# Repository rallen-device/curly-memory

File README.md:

# CURLY-MEMORY

Open source eurorack hardware using an ESP32.

ESP32 acts like anything you want, just reprogram with new firmware.

## Features

### INPUTS:
 - Analogue input x4
  - 1/8" jack x3 (IN0, IN1, IN2)
  - 2.54mm pin header x2 (IN2, IN3)

### OUTPUTS:
 - Analogue output x4
  - 1/8" jack x3 (OUT0, OUT1, OUT2)
  - 2.54mm pin header x3 (OUT2, OUT3)

### CONTROLS:
 - Potentiometer input x4
 - Tactile switch x2

### OTHER:
 - Feedback resistor (digital pot connecting OUT0 to IN0)
 - Digital pot output on 2.54mm pin header
 - Dry/wet mixer (IN0 + OUT0 - connecting to digital pot)
 - WS2812B LEDs x2

### POWER:
 - Eurorack standard 10 pin IDC connector
 - 12V input

### FIRMWARE:
 - ESP-IDF or Arduino

## Images

## References

- https://www.electrosmash.com/pt2399-analysis
- https://intellijel.com/support/eurorack-101/
- https://docs.espressif.com/projects/esp-idf/en/latest/esp32/api-reference/peripherals/spi_master.html

## Influences

- https://ornament-and-cri.me/

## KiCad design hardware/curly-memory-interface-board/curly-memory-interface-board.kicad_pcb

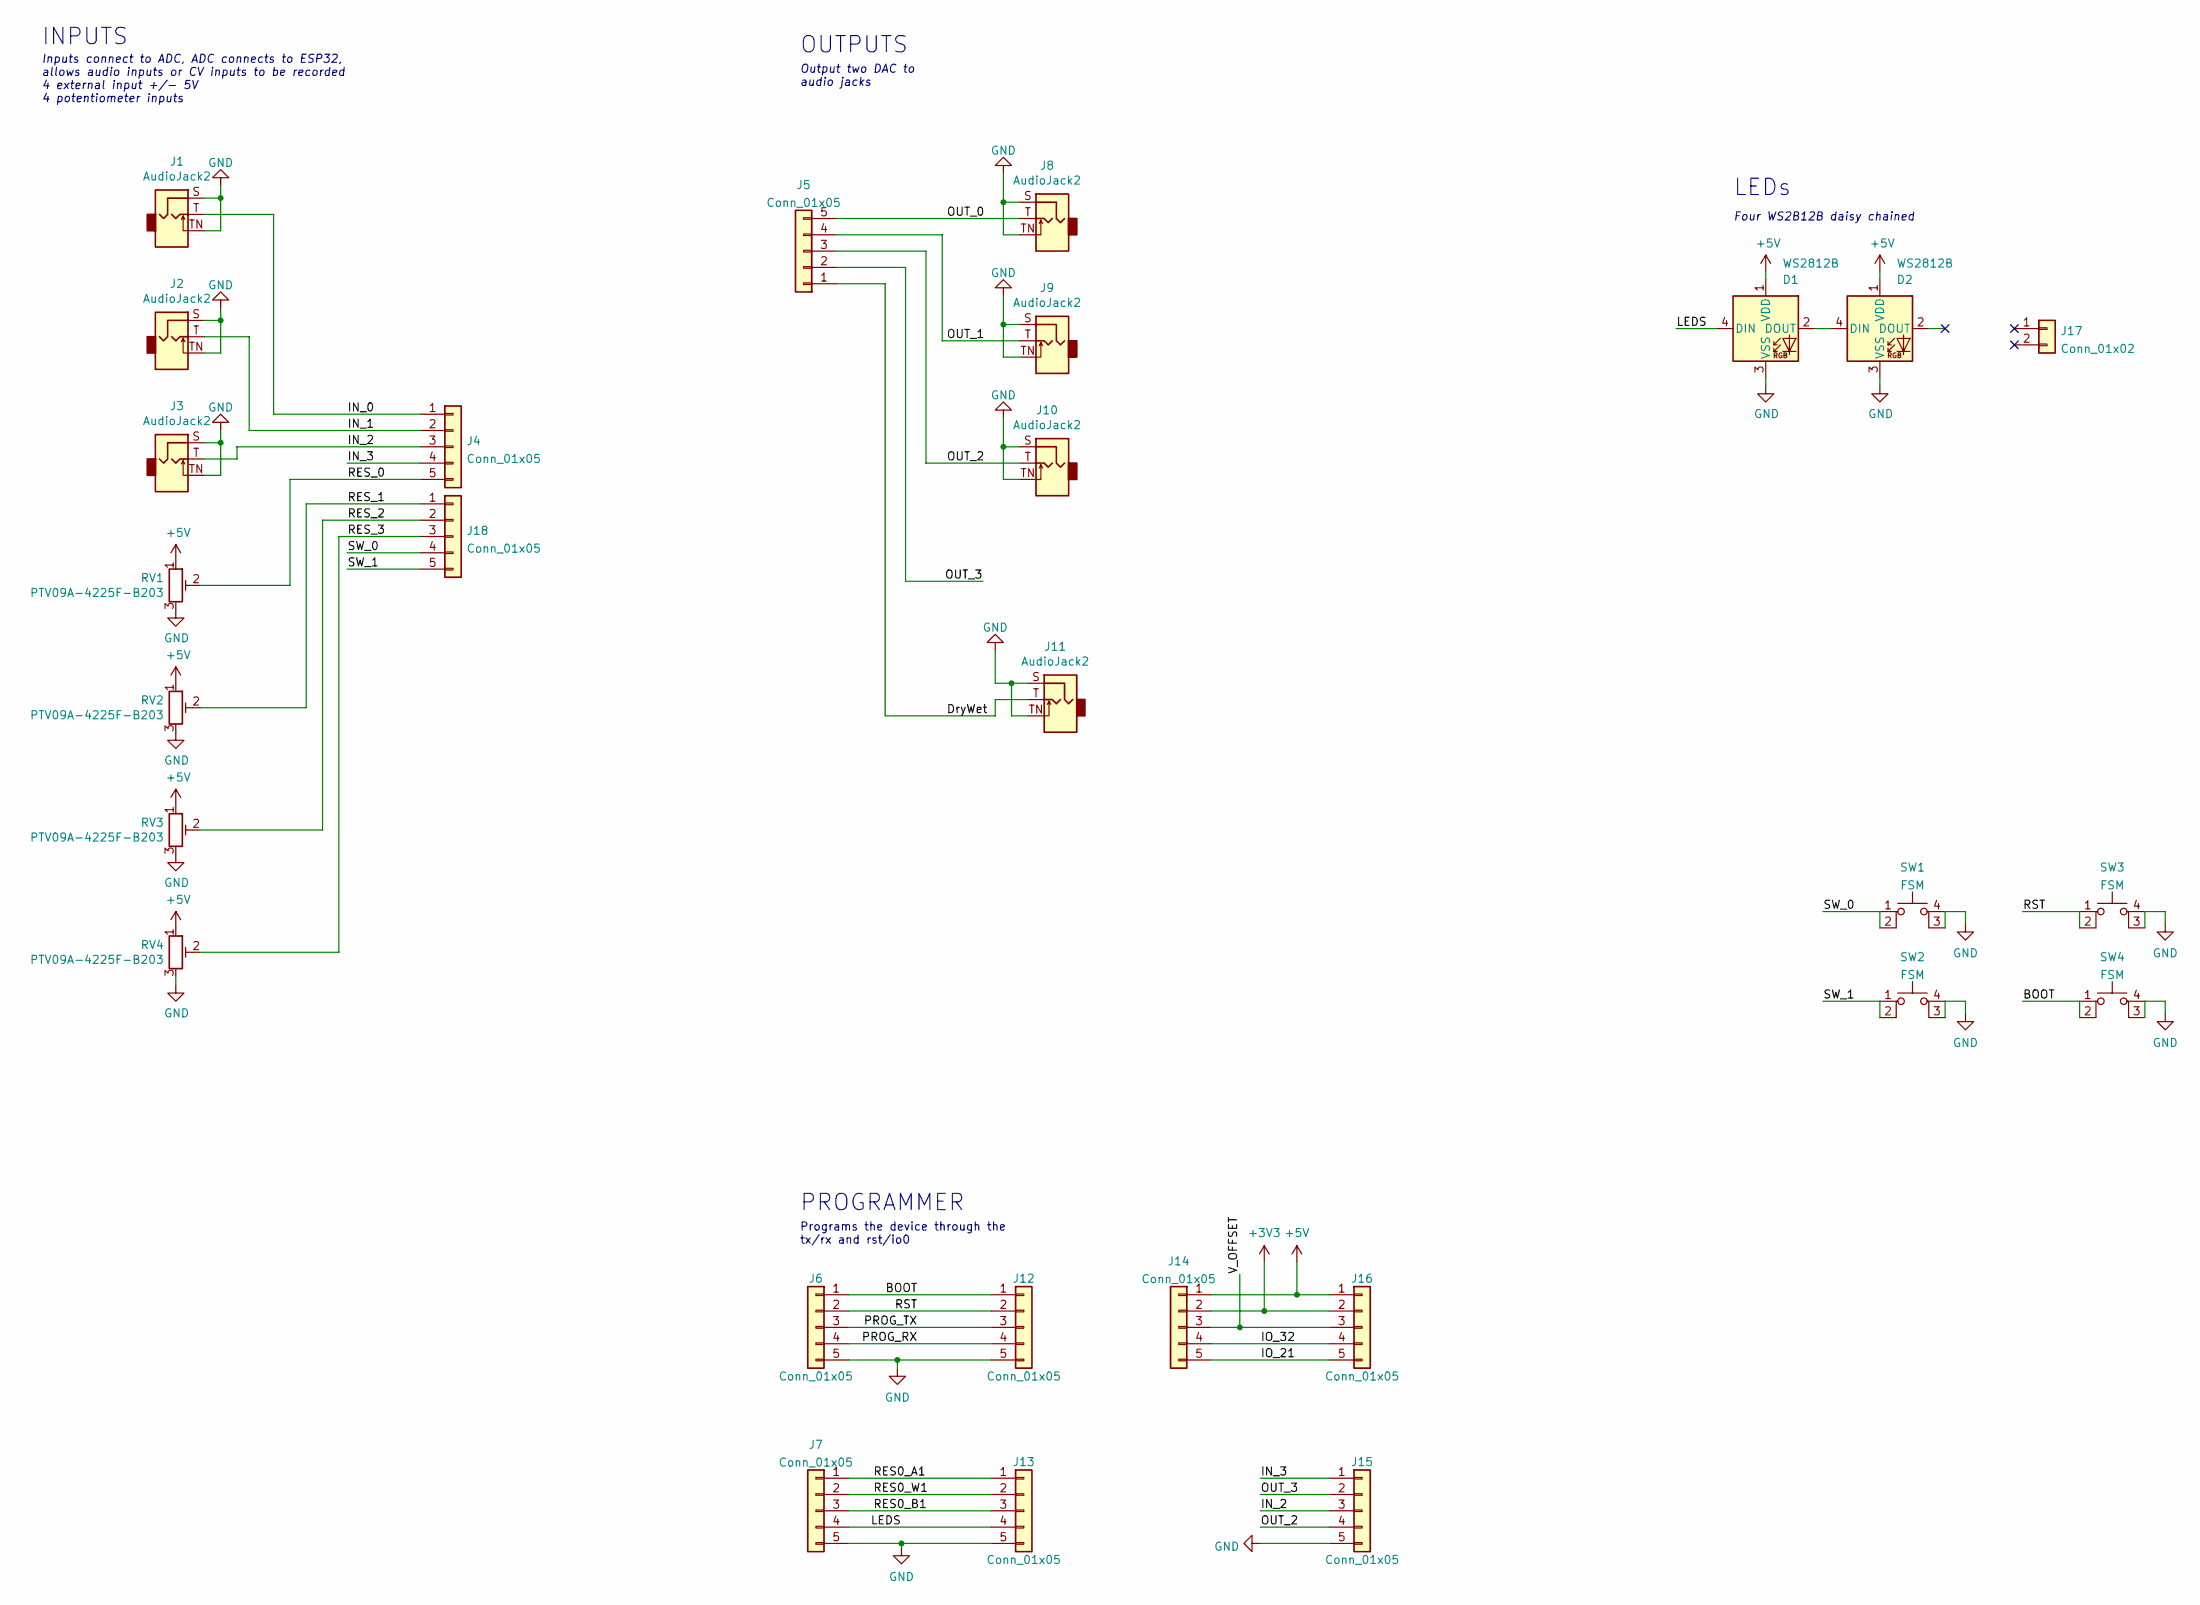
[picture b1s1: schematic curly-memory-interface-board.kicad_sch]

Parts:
D1, D2: WS2812B; LED_WS2812B_PLCC4_5.0x5.0mm_P3.2mm
J1, J2, J3, J8, J9, J10, J11: AudioJack2; Jack_3.5mm_QingPu_WQP-PJ398SM_Vertical
J4, J5, J6, J7, J14, J18: Conn_01x05; PinSocket_1x05_P2.54mm_Vertical
J12, J13, J15, J16: Conn_01x05; PinHeader_1x05_P2.54mm_Vertical
J17: Conn_01x02; PinSocket_1x02_P2.54mm_Vertical
RV1, RV2, RV3, RV4: PTV09A-4225F-B203; Potentiometer_Bourns_PTV09A-1_Single_Vertical
SW1, SW2, SW3, SW4: FSM; SW_Push_1P1T_NO_6x6mm_H9.5mm

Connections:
+3V3: J14.2, J16.2
+5V: D1.1 (VDD), D2.1 (VDD), J14.1, J16.1, RV1.1, RV2.1, RV3.1, RV4.1
/BOOT: J6.1, J12.1, SW4.1, SW4.2
/DryWet: J5.1, J11.T
/IN_0: J1.T, J4.1
/IN_1: J2.T, J4.2
/IN_2: J3.T, J4.3, J15.3
/IN_3: J4.4, J15.1
/IO_21: J14.5, J16.5
/IO_32: J14.4, J16.4
/LEDS: D1.4 (DIN), J7.4, J13.4
/OUT_0: J5.5, J8.T
/OUT_1: J5.4, J9.T
/OUT_2: J5.3, J10.T, J15.4
/OUT_3: J5.2, J15.2
/PROG_RX: J6.4, J12.4
/PROG_TX: J6.3, J12.3
/RES0_A1: J7.1, J13.1
/RES0_B1: J7.3, J13.3
/RES0_W1: J7.2, J13.2
/RES_0: J4.5, RV1.2
/RES_1: J18.1, RV2.2
/RES_2: J18.2, RV3.2
/RES_3: J18.3, RV4.2
/RST: J6.2, J12.2, SW3.1, SW3.2
/SW_0: J18.4, SW1.1, SW1.2
/SW_1: J18.5, SW2.1, SW2.2
/V_OFFSET: J14.3, J16.3
GND: D1.3 (VSS), D2.3 (VSS), J1.S, J1.TN, J2.S, J2.TN, J3.S, J3.TN, J6.5, J7.5, J8.S, J8.TN, J9.S, J9.TN, J10.S, J10.TN, J11.S, J11.TN, J12.5, J13.5, J15.5, RV1.3, RV2.3, RV3.3, RV4.3, SW1.3 (K), SW1.4 (A), SW2.3 (K), SW2.4 (A), SW3.3 (K), SW3.4 (A), SW4.3 (K), SW4.4 (A)
unnamed: D1.2 (DOUT), D2.4 (DIN)

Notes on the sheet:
INPUTS
OUTPUTS
LEDs
Programs the device through the tx/rx and rst/io0
Output two DAC to audio jacks
Four WS2B12B daisy chained
PROGRAMMER
Inputs connect to ADC, ADC connects to ESP32, allows audio inputs or CV inputs to be recorded 4 external input +/- 5V 4 potentiometer inputs

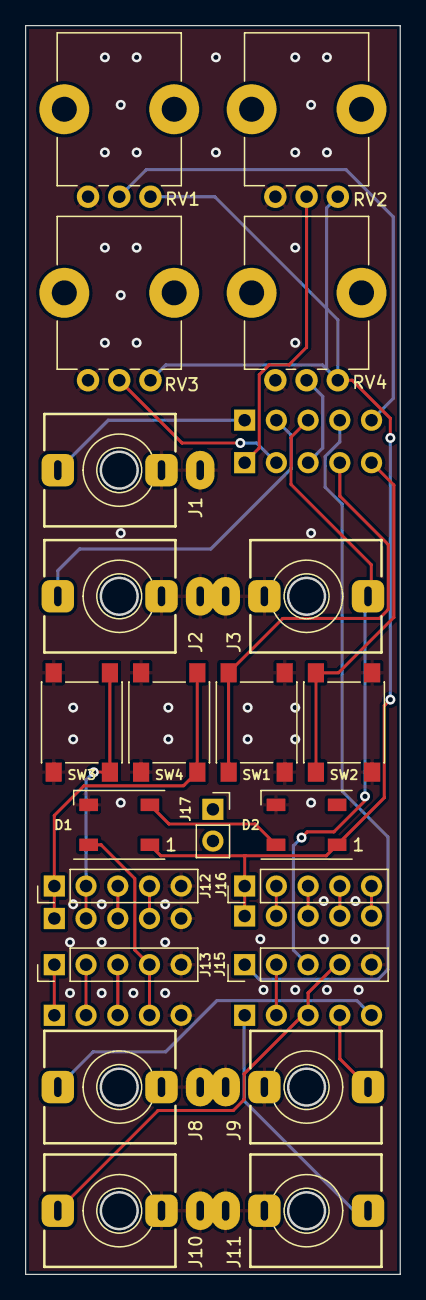
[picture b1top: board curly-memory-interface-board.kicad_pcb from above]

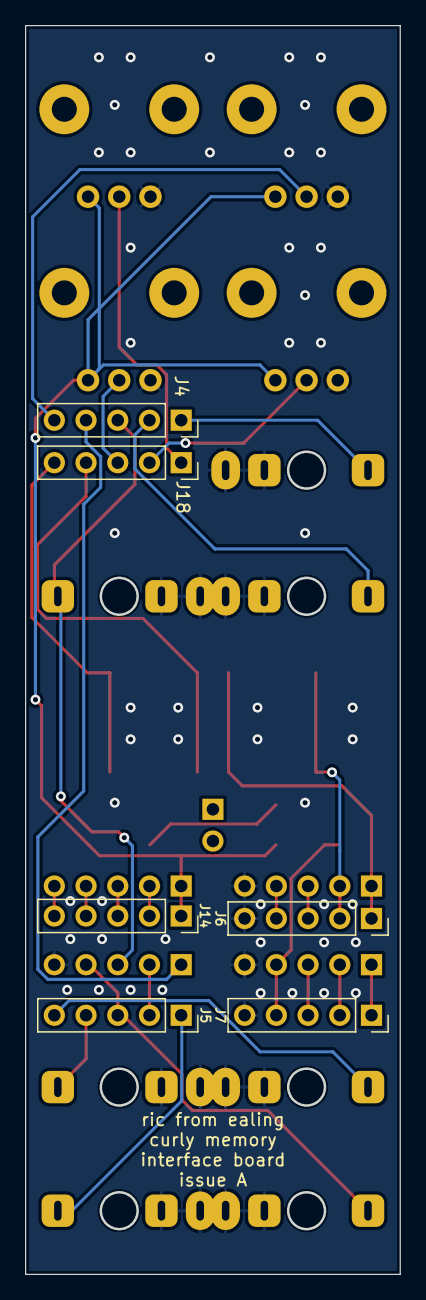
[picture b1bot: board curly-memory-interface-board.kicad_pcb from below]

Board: 2 copper layers, 30.0 x 100.0 mm, 28 parts (6 on the bottom side), 30 nets.

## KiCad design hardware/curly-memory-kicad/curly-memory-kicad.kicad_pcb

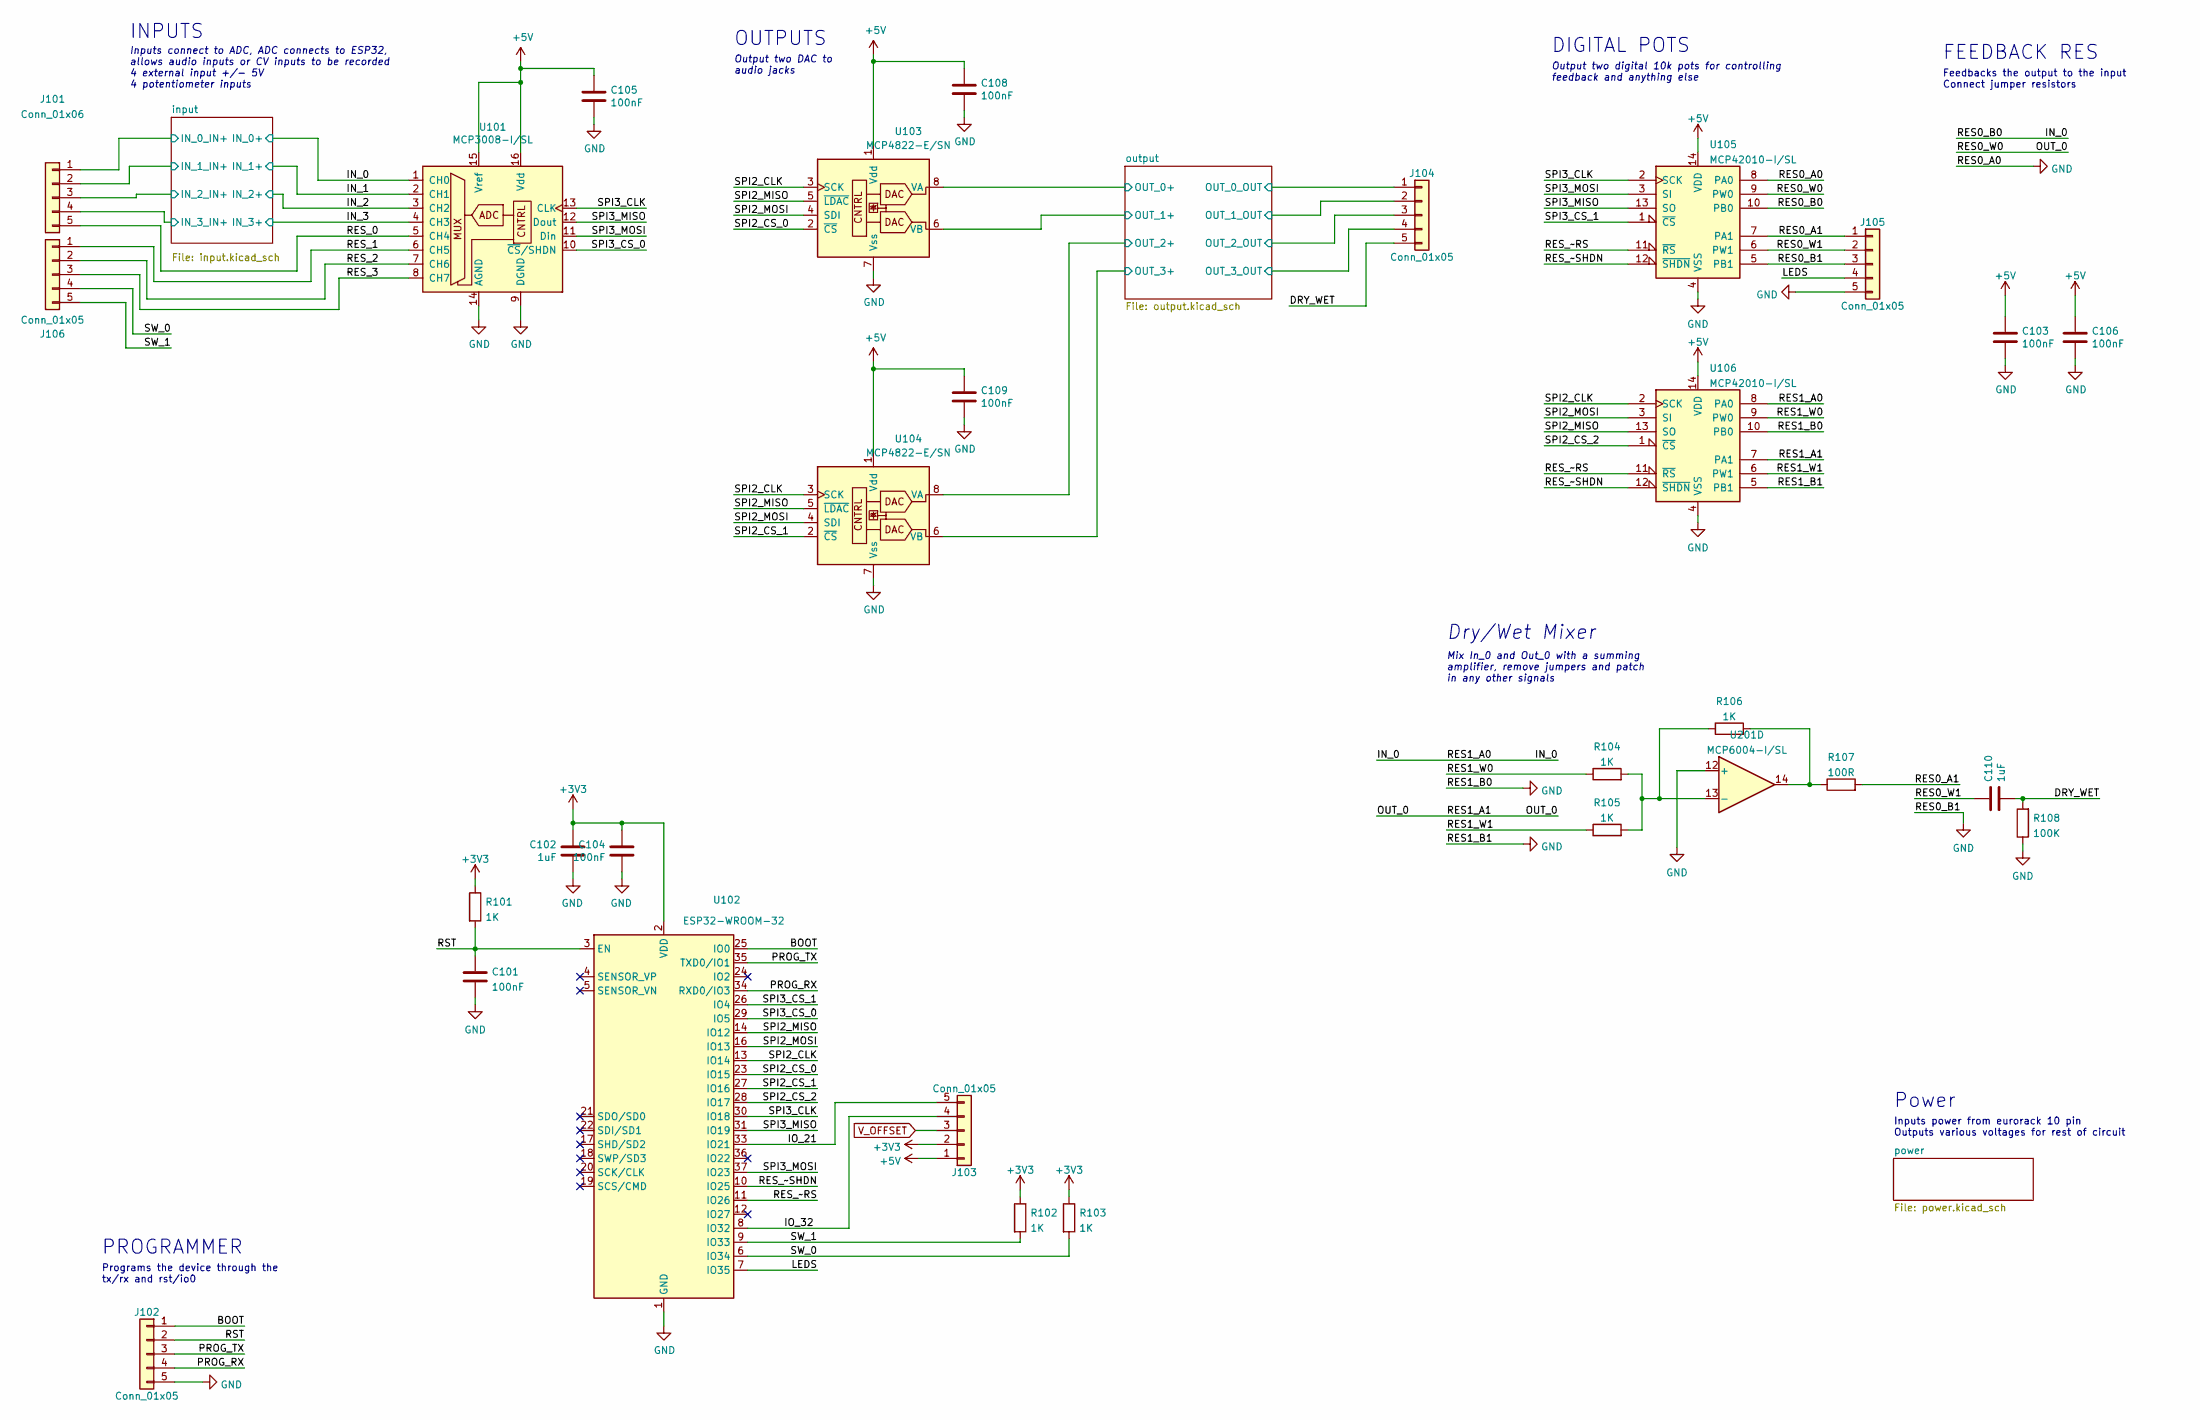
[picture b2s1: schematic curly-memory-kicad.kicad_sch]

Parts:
C101, C103, C104, C105, C106, C108, C109: 100nF; C_0805_2012Metric_Pad1.18x1.45mm_HandSolder; Voltage 50V
C102, C110: 1uF; C_0805_2012Metric_Pad1.18x1.45mm_HandSolder; Voltage 50V
J101: Conn_01x06; PinHeader_1x05_P2.54mm_Vertical
J102, J103, J104, J105, J106: Conn_01x05; PinHeader_1x05_P2.54mm_Vertical
R101, R102, R103, R104, R105, R106: 1K; R_0805_2012Metric_Pad1.20x1.40mm_HandSolder; Tolerance 1%
R107: 100R; R_0805_2012Metric_Pad1.20x1.40mm_HandSolder; Tolerance 1%
R108: 100K; R_0805_2012Metric_Pad1.20x1.40mm_HandSolder; Tolerance 1%
U101: MCP3008-I/SL; SOIC-16_3.9x9.9mm_P1.27mm
U102: ESP32-WROOM-32
U103, U104: MCP4822-E/SN; SOIC-8_3.9x4.9mm_P1.27mm
U105, U106: MCP42010-I/SL; SOIC-14_3.9x8.7mm_P1.27mm
U201: MCP6004-I/SL; SOIC-14_3.9x8.7mm_P1.27mm

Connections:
+3V3: C102.1, C104.1, J103.2, R101.1, R102.1, R103.1, U102.2 (VDD); also elsewhere on the board
+5V: C103.1, C105.1, C106.1, C108.1, C109.1, J103.1, U101.15 (Vref), U101.16 (Vdd), U103.1 (Vdd), U104.1 (Vdd), U105.14 (VDD), U106.14 (VDD); also elsewhere on the board
/BOOT: J102.1, U102.25 (IO0)
/DRY_WET: C110.2, J104.5, R108.2
/IN_0: U101.1 (CH0), U105.10 (PB0), U106.8 (PA0); also elsewhere on the board
/IN_1: U101.2 (CH1); also elsewhere on the board
/IN_2: U101.3 (CH2); also elsewhere on the board
/IN_3: J101.4, U101.4 (CH3); also elsewhere on the board
/IO_21: J103.5, U102.33 (IO21)
/IO_32: J103.4, U102.8 (IO32)
/LEDS: J105.4, U102.7 (IO35)
/OUT_0: U105.9 (PW0), U106.7 (PA1)
/PROG_RX: J102.4, U102.34 (RXD0/IO3)
/PROG_TX: J102.3, U102.35 (TXD0/IO1)
/RES0_A1: J105.1, R107.2, U105.7 (PA1)
/RES0_W1: C110.1, J105.2, U105.6 (PW1)
/RES1_W0: R104.1, U106.9 (PW0)
/RES1_W1: R105.1, U106.6 (PW1)
/RES_0: J101.5, U101.5 (CH4)
/RES_1: J106.1, U101.6 (CH5)
/RES_2: J106.2, U101.7 (CH6)
/RES_3: J106.3, U101.8 (CH7)
/RES_~RS: U102.11 (IO26), U105.11 (~RS), U106.11 (~RS)
/RES_~SHDN: U102.10 (IO25), U105.12 (~SHDN), U106.12 (~SHDN)
/RST: C101.1, J102.2, R101.2, U102.3 (EN)
/SPI2_CLK: U102.13 (IO14), U103.3 (SCK), U104.3 (SCK), U106.2 (SCK)
/SPI2_CS_0: U102.23 (IO15), U103.2 (~CS)
/SPI2_CS_1: U102.27 (IO16), U104.2 (~CS)
/SPI2_CS_2: U102.28 (IO17), U106.1 (~CS)
/SPI2_MISO: U102.14 (IO12), U103.5 (~LDAC), U104.5 (~LDAC), U106.13 (SO)
/SPI2_MOSI: U102.16 (IO13), U103.4 (SDI), U104.4 (SDI), U106.3 (SI)
/SPI3_CLK: U101.13 (CLK), U102.30 (IO18), U105.2 (SCK)
/SPI3_CS_0: U101.10 (~CS/SHDN), U102.29 (IO5)
/SPI3_CS_1: U102.26 (IO4), U105.1 (~CS)
/SPI3_MISO: U101.12 (Dout), U102.31 (IO19), U105.13 (SO)
/SPI3_MOSI: U101.11 (Din), U102.37 (IO23), U105.3 (SI)
/SW_0: J106.4, R103.2, U102.6 (IO34)
/SW_1: J106.5, R102.2, U102.9 (IO33)
/input/IN_0_IN+: J101.1; also elsewhere on the board
/input/IN_1_IN+: J101.2; also elsewhere on the board
/input/IN_2_IN+: J101.3; also elsewhere on the board
/output/OUT_0+: U103.8 (VA); also elsewhere on the board
/output/OUT_0_OUT: J104.1; also elsewhere on the board
/output/OUT_1+: U103.6 (VB); also elsewhere on the board
/output/OUT_1_OUT: J104.2; also elsewhere on the board
/output/OUT_2+: U104.8 (VA); also elsewhere on the board
/output/OUT_2_OUT: J104.3; also elsewhere on the board
/output/OUT_3+: J104.4, U104.6 (VB)
GND: C101.2, C102.2, C103.2, C104.2, C105.2, C106.2, C108.2, C109.2, J102.5, J105.3, J105.5, R108.1, U101.9 (DGND), U101.14 (AGND), U102.1 (GND), U102.15 (GND), U102.38 (GND), U102.39 (GND), U103.7 (Vss), U104.7 (Vss), U105.4 (VSS), U105.5 (PB1), U105.8 (PA0), U106.4 (VSS), U106.5 (PB1), U106.10 (PB0), U201.12 (+); also elsewhere on the board
unnamed: R104.2, R105.2, R106.1, U201.13 (-)
unnamed: R106.2, R107.1, U201.14
V_OFFSET: J103.3; also elsewhere on the board

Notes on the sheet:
DIGITAL POTS
Inputs power from eurorack 10 pin Outputs various voltages for rest of circuit
INPUTS
FEEDBACK RES
Power
Output two digital 10k pots for controlling feedback and anything else
OUTPUTS
Programs the device through the tx/rx and rst/io0
Output two DAC to audio jacks
Mix In_0 and Out_0 with a summing amplifier, remove jumpers and patch in any other signals
PROGRAMMER
Dry/Wet Mixer
Inputs connect to ADC, ADC connects to ESP32, allows audio inputs or CV inputs to be recorded 4 external input +/- 5V 4 potentiometer inputs
Feedbacks the output to the input Connect jumper resistors

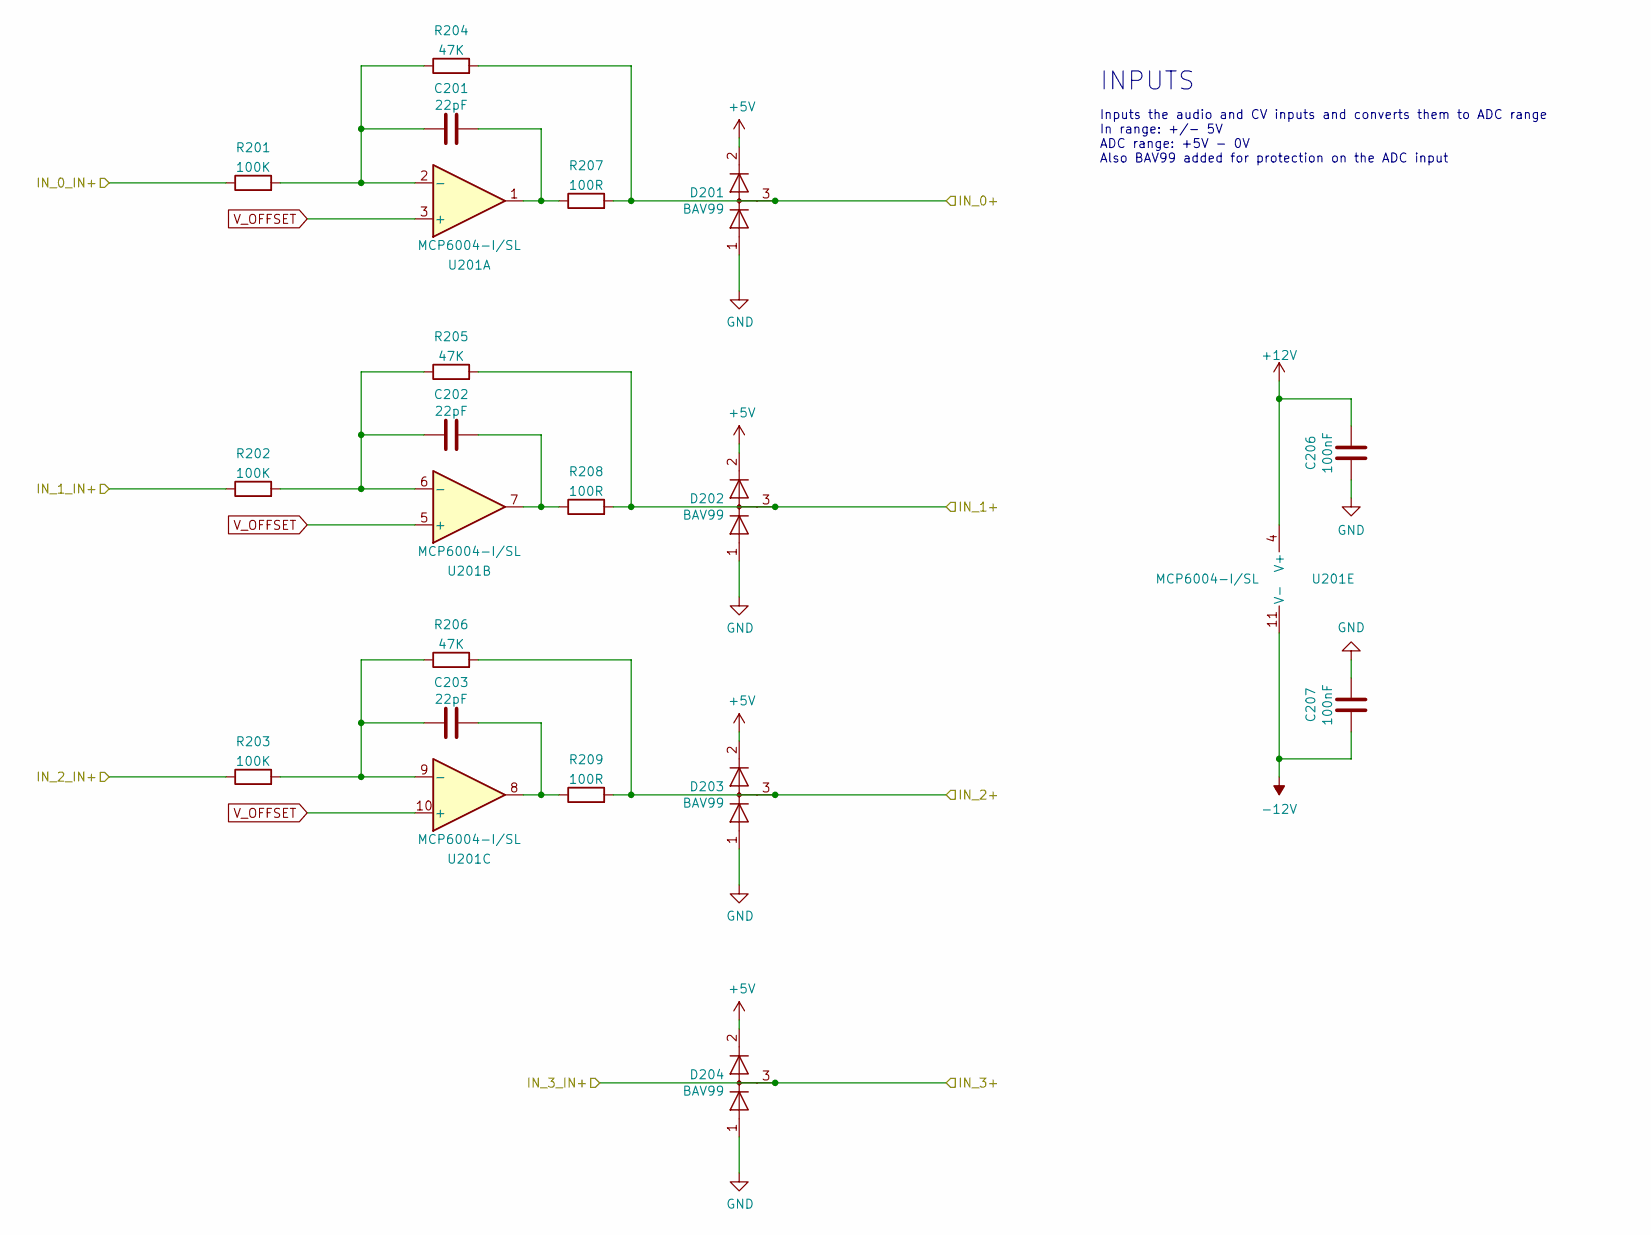
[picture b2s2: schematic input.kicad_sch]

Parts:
C201, C202, C203: 22pF; C_0805_2012Metric_Pad1.18x1.45mm_HandSolder; Voltage 50V
C206, C207: 100nF; C_0805_2012Metric_Pad1.18x1.45mm_HandSolder; Voltage 50V
D201, D202, D203, D204: BAV99; SOT-23
R201, R202, R203: 100K; R_0805_2012Metric_Pad1.20x1.40mm_HandSolder; Tolerance 1%
R204, R205, R206: 47K; R_0805_2012Metric_Pad1.20x1.40mm_HandSolder; Tolerance 1%
R207, R208, R209: 100R; R_0805_2012Metric_Pad1.20x1.40mm_HandSolder; Tolerance 1%
U201: MCP6004-I/SL; SOIC-14_3.9x8.7mm_P1.27mm

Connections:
+5V: D201.2 (A), D202.2 (A), D203.2 (A), D204.2 (A); also elsewhere on the board
+12V: C206.1, U201.4 (V+); also elsewhere on the board
-12V: C207.1, U201.11 (V-); also elsewhere on the board
/IN_0: D201.3 (K), R204.2, R207.2; also elsewhere on the board
/IN_1: D202.3 (K), R205.2, R208.2; also elsewhere on the board
/IN_2: D203.3 (K), R206.2, R209.2; also elsewhere on the board
/IN_3: D204.3 (K); also elsewhere on the board
/input/IN_0_IN+: R201.1; also elsewhere on the board
/input/IN_1_IN+: R202.1; also elsewhere on the board
/input/IN_2_IN+: R203.1; also elsewhere on the board
GND: C206.2, C207.2, D201.1 (K), D202.1 (K), D203.1 (K), D204.1 (K); also elsewhere on the board
unnamed: C201.1, R207.1, U201.1
unnamed: C201.2, R201.2, R204.1, U201.2 (-)
unnamed: C202.1, R208.1, U201.7
unnamed: C202.2, R202.2, R205.1, U201.6 (-)
unnamed: C203.1, R209.1, U201.8
unnamed: C203.2, R203.2, R206.1, U201.9 (-)
V_OFFSET: U201.3 (+), U201.5 (+), U201.10 (+); also elsewhere on the board

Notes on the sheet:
Inputs the audio and CV inputs and converts them to ADC range In range: +/- 5V ADC range: +5V - 0V Also BAV99 added for protection on the ADC input
INPUTS

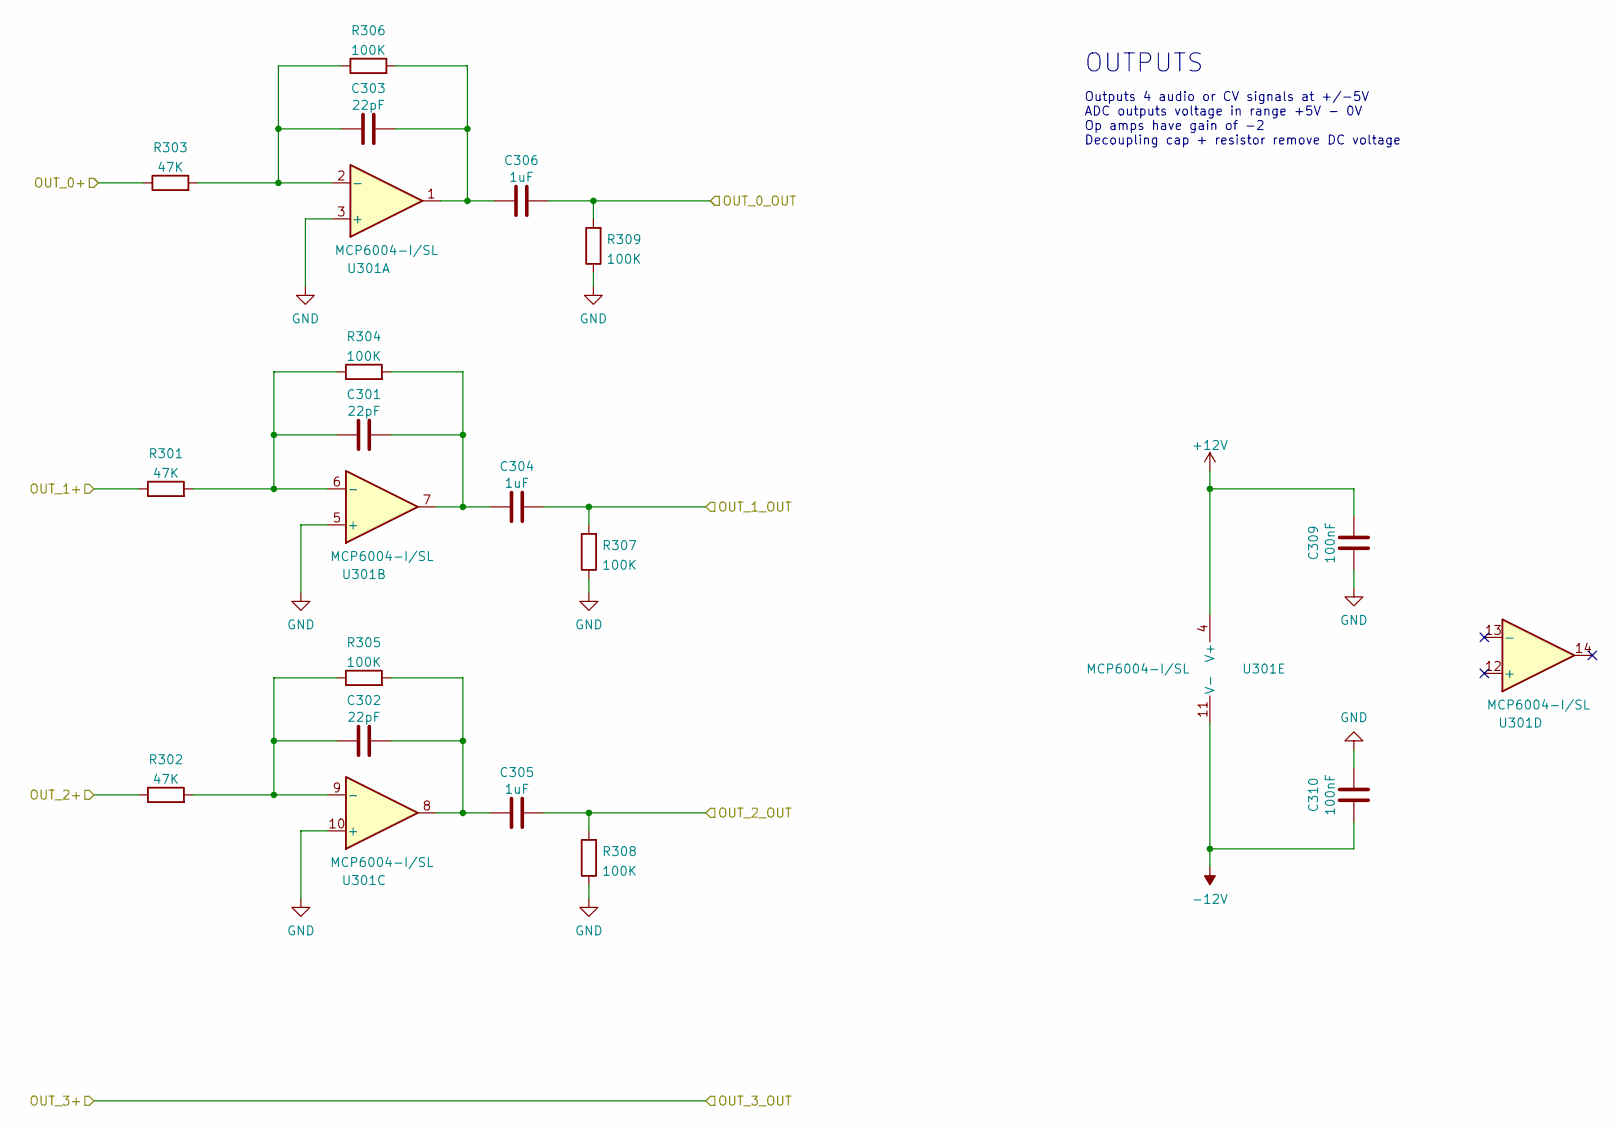
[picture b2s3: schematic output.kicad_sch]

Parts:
C301, C302, C303: 22pF; C_0805_2012Metric_Pad1.18x1.45mm_HandSolder; Voltage 50V
C304, C305, C306: 1uF; C_0805_2012Metric_Pad1.18x1.45mm_HandSolder; Voltage 50V
C309, C310: 100nF; C_0805_2012Metric_Pad1.18x1.45mm_HandSolder; Voltage 50V
R301, R302, R303: 47K; R_0805_2012Metric_Pad1.20x1.40mm_HandSolder; Tolerance 1%
R304, R305, R306, R307, R308, R309: 100K; R_0805_2012Metric_Pad1.20x1.40mm_HandSolder; Tolerance 1%
U301: MCP6004-I/SL; SOIC-14_3.9x8.7mm_P1.27mm

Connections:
+12V: C309.1, U301.4 (V+); also elsewhere on the board
-12V: C310.1, U301.11 (V-); also elsewhere on the board
/output/OUT_0+: R303.1; also elsewhere on the board
/output/OUT_0_OUT: C306.1, R309.2; also elsewhere on the board
/output/OUT_1+: R301.1; also elsewhere on the board
/output/OUT_1_OUT: C304.1, R307.2; also elsewhere on the board
/output/OUT_2+: R302.1; also elsewhere on the board
/output/OUT_2_OUT: C305.1, R308.2; also elsewhere on the board
GND: C309.2, C310.2, R307.1, R308.1, R309.1, U301.3 (+), U301.5 (+), U301.10 (+); also elsewhere on the board
unnamed: C301.1, C304.2, R304.2, U301.7
unnamed: C301.2, R301.2, R304.1, U301.6 (-)
unnamed: C302.1, C305.2, R305.2, U301.8
unnamed: C302.2, R302.2, R305.1, U301.9 (-)
unnamed: C303.1, C306.2, R306.2, U301.1
unnamed: C303.2, R303.2, R306.1, U301.2 (-)

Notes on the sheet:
OUTPUTS
Outputs 4 audio or CV signals at +/-5V ADC outputs voltage in range +5V - 0V Op amps have gain of -2 Decoupling cap + resistor remove DC voltage

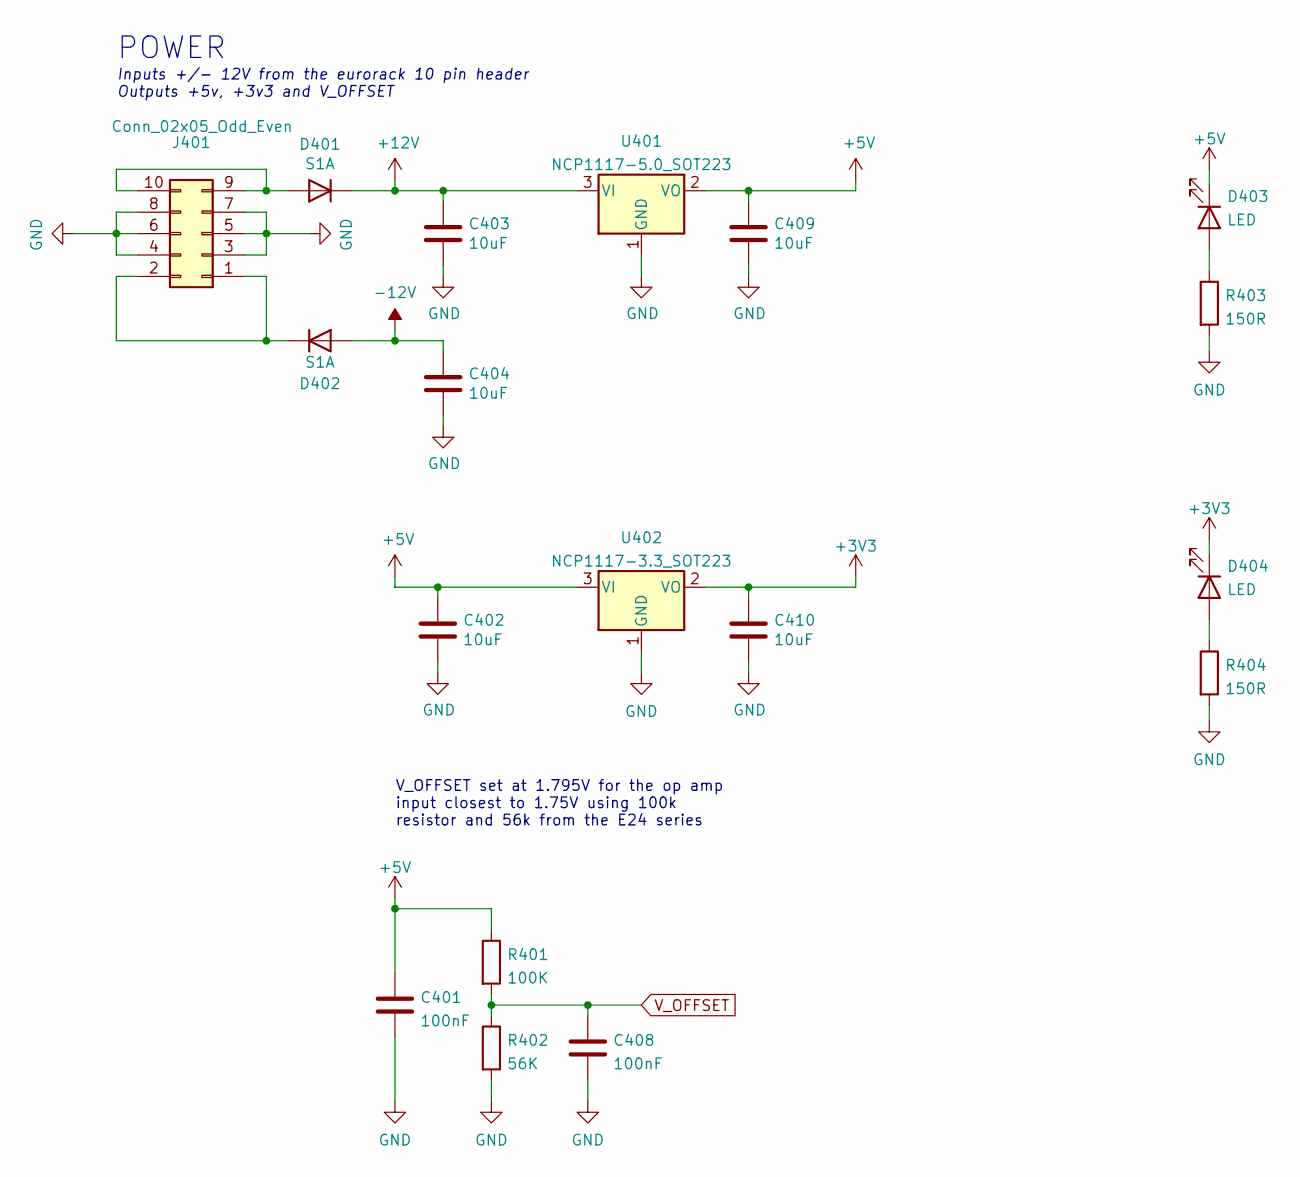
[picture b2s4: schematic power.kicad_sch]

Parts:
C401, C408: 100nF; C_0805_2012Metric_Pad1.18x1.45mm_HandSolder; Voltage 50V
C402, C403, C404, C409, C410: 10uF; C_0805_2012Metric_Pad1.18x1.45mm_HandSolder; Voltage 50V
D401, D402: S1A; D_SMA
D403, D404: LED; LED_0805_2012Metric_Pad1.15x1.40mm_HandSolder
J401: Conn_02x05_Odd_Even; IDC-Header_2x05_P2.54mm_Horizontal
R401: 100K; R_0805_2012Metric_Pad1.20x1.40mm_HandSolder; Tolerance 1%
R402: 56K; R_0805_2012Metric_Pad1.20x1.40mm_HandSolder; Tolerance 1%
R403, R404: 150R; R_0805_2012Metric_Pad1.20x1.40mm_HandSolder; Tolerance 1%
U401: NCP1117-5.0_SOT223; SOT-223-3_TabPin2; Voltage 5V
U402: NCP1117-3.3_SOT223; SOT-223-3_TabPin2; Voltage 3V3

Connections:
+3V3: C410.1, D404.1 (K), U402.2 (VO); also elsewhere on the board
+5V: C401.1, C402.1, C409.1, D403.1 (K), R401.1, U401.2 (VO), U402.3 (VI); also elsewhere on the board
+12V: C403.1, D401.1 (K), U401.3 (VI); also elsewhere on the board
-12V: C404.1, D402.2 (A); also elsewhere on the board
GND: C401.2, C402.2, C403.2, C404.2, C408.2, C409.2, C410.2, J401.3, J401.4, J401.5, J401.6, J401.7, J401.8, R402.2, R403.2, R404.2, U401.1 (GND), U402.1 (GND); also elsewhere on the board
unnamed: D401.2 (A), J401.9, J401.10
unnamed: D402.1 (K), J401.1, J401.2
unnamed: D403.2 (A), R403.1
unnamed: D404.2 (A), R404.1
V_OFFSET: C408.1, R401.2, R402.1; also elsewhere on the board

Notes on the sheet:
V_OFFSET set at 1.795V for the op amp input closest to 1.75V using 100k resistor and 56k from the E24 series
POWER
Inputs +/- 12V from the eurorack 10 pin header Outputs +5v, +3v3 and V_OFFSET

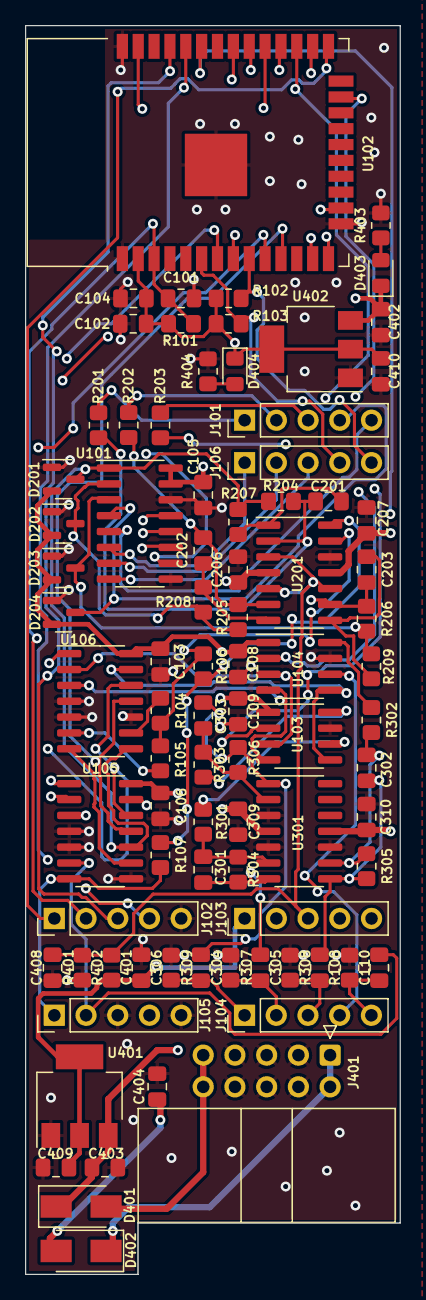
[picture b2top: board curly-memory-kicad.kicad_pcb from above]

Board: 4 copper layers, 30.0 x 100.0 mm, 84 parts (0 on the bottom side), 70 nets.

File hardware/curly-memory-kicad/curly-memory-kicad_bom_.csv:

Component,Part,Description,References,Value,Footprint,Quantity Per PCB,Datasheet,MF,MFPN,Material,Voltage,Tolerance
1,C,Unpolarized capacitor,C201 C202 C203 C301 C302 C303,22pF,C_0805_2012Metric_Pad1.18x1.45mm_HandSolder,6,,Samsung,CL21C220JBANNNC,CG0 / NP0,50V,
2,C_1,Unpolarized capacitor,C101 C103 C104 C105 C106 C108 C109 C206 C207 C309 C310 C401 C408,100nF,C_0805_2012Metric_Pad1.18x1.45mm_HandSolder,13,~,Samsung,CL21B104KBCNNNC,X7R,50V,
3,C,,C102 C110 C304 C305 C306,1uF,C_0805_2012Metric_Pad1.18x1.45mm_HandSolder,5,,Samsung,CL21B105KBFNNNE,X7R,50V,
4,C,,C402 C403 C404 C409 C410,10uF,C_0805_2012Metric_Pad1.18x1.45mm_HandSolder,5,,Murata,GRM21BR61H106KE43L,X5R,50V,
5,BAV99,,D201 D202 D203 D204,BAV99,SOT-23,4,https://assets.nexperia.com/documents/data-sheet/BAV99_SER.pdf,,,,,
6,LED,Light emitting diode,D403 D404,LED,LED_0805_2012Metric_Pad1.15x1.40mm_HandSolder,2,~,Kingbright,KP-2012EC,,,
7,D,,D401 D402,S1A,D_SMA,2,,,,,,
8,R,Resistor,R107 R207 R208 R209,100R,R_0805_2012Metric_Pad1.20x1.40mm_HandSolder,4,~,Multicomp,MCWR08X1000FTL,,,1%
9,R,Resistor,R403 R404,150R,R_0805_2012Metric_Pad1.20x1.40mm_HandSolder,2,~,Multicomp,MCWR08X1500FTL,,,1%
10,R_1,Resistor,R101 R102 R103 R104 R105 R106,1K,R_0805_2012Metric_Pad1.20x1.40mm_HandSolder,6,~,Multicomp,MCWR08X1001FTL,,,1%
11,R,Resistor,R204 R205 R206 R301 R302 R303,47K,R_0805_2012Metric_Pad1.20x1.40mm_HandSolder,6,~,Multicomp,MCWR08X4702FTL,,,1%
12,R,Resistor,R402,56K,R_0805_2012Metric_Pad1.20x1.40mm_HandSolder,1,~,Multicomp,MCWR08X5602FTL,,,1%
13,R,Resistor,R108 R201 R202 R203 R304 R305 R306 R307 R308 R309 R401,100K,R_0805_2012Metric_Pad1.20x1.40mm_HandSolder,11,~,Multicomp,MCWR08X1003FTL,,,1%
14,ESP32-WROOM-32,,U102,ESP32-WROOM-32,ESP32-WROOM-32,1,https://www.espressif.com/sites/default/files/documentation/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,,,,,
15,MCP3008,,U101,MCP3008-I/SL,SOIC-16_3.9x9.9mm_P1.27mm,1,http://ww1.microchip.com/downloads/en/DeviceDoc/21295d.pdf,,,,,
16,MCP42010,"Dual Digital Potentiometer, SPI interface, 256 taps, 10 kohm",U105 U106,MCP42010-I/SL,SOIC-14_3.9x8.7mm_P1.27mm,2,http://ww1.microchip.com/downloads/en/DeviceDoc/11195c.pdf,,,,,
17,MCP4822,,U103 U104,MCP4822-E/SN,SOIC-8_3.9x4.9mm_P1.27mm,2,http://ww1.microchip.com/downloads/en/DeviceDoc/20002249B.pdf,,,,,
18,MCP6004,"1MHz, Low-Power Op Amp, DIP-14/SOIC-14/TSSOP-14",U201 U301,MCP6004-I/SL,SOIC-14_3.9x8.7mm_P1.27mm,2,http://ww1.microchip.com/downloads/en/DeviceDoc/21733j.pdf,,,,,
19,NCP1117-3.3_SOT223,"1A Low drop-out regulator, Fixed Output 3.3V, SOT-223",U402,NCP1117-3.3_SOT223,SOT-223-3_TabPin2,1,http://www.onsemi.com/pub_link/Collateral/NCP1117-D.PDF,STMICROELECTRONICS,LD1117S33TR,,3V3,
20,NCP1117-5.0_SOT223,"1A Low drop-out regulator, Fixed Output 5V, SOT-223",U401,NCP1117-5.0_SOT223,SOT-223-3_TabPin2,1,http://www.onsemi.com/pub_link/Collateral/NCP1117-D.PDF,STMICROELECTRONICS,LD1117S50TR,,5V,





Component Groups:,20
Component Count:,77
Fitted Components:,77
Number of PCBs:,1
Total components:,77
Schematic Version:,
Schematic Date:,
PCB Variant:,default
BoM Date:,"Sunday, 16 January 2022 at 09:36:38"
Schematic Source:,curly-memory-kicad.kicad_sch
KiCad Version:,Eeschema (6.0.0-0)

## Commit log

2021-12-12 added initial commit for the kicad hardware, added component list and osc_in circuit picture
2021-12-18 software readme added
2021-12-18 gitignore added
2021-12-18 .ds_store removed
2021-12-18 initial commit for firmware
2021-12-21 more software added, ability to change digital pots
2021-12-21 readme updated to reflect status of project
2021-12-21 Create LICENSE
2021-12-23 hardware update to relfect latest version of projectm gitignore updated to ignore *-bak files
2021-12-25 update to delay software, remember to turn off wdt in menuconfig
2021-12-25 more dleay working
2021-12-29 hardware schematic updated to kicad6, extra components added: 2nd digital pot, rotary encoder, tactile switch x2, wet/dry mix going to out1
2021-12-29 readme updated
2021-12-30 hardware updated, added todo
2021-12-30 update todo
2022-01-02 output + input op amps added, simuatlion added to sim folder
2022-01-02 updated todo
2022-01-06 schematic updated with component fields on more components
2022-01-08 all components have part numbers
2022-01-09 interface board added
2022-01-11 all components placed on the main board
2022-01-15 more pcb tracked
2022-01-15 more pcb tracked- again
2022-01-15 silkscreen lined up lovely
2022-01-15 interface board tracked and silkscreen sorted
2022-01-15 all hardware finished
2022-01-16 gerbers genearted and mf/mfpn added for main board for build
2022-01-24 pcbs sent off to pcbway for issue A
2022-01-24 some images added for readme.md
2022-01-24 readme updated to add image
2022-01-24 try again
2022-01-24 will this commit work?
2022-01-24 put the brackets the right way round
2022-01-24 update readme with all images
